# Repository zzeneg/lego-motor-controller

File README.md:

# lego-motor-controller
Control your Lego PF motors with Bluetooth

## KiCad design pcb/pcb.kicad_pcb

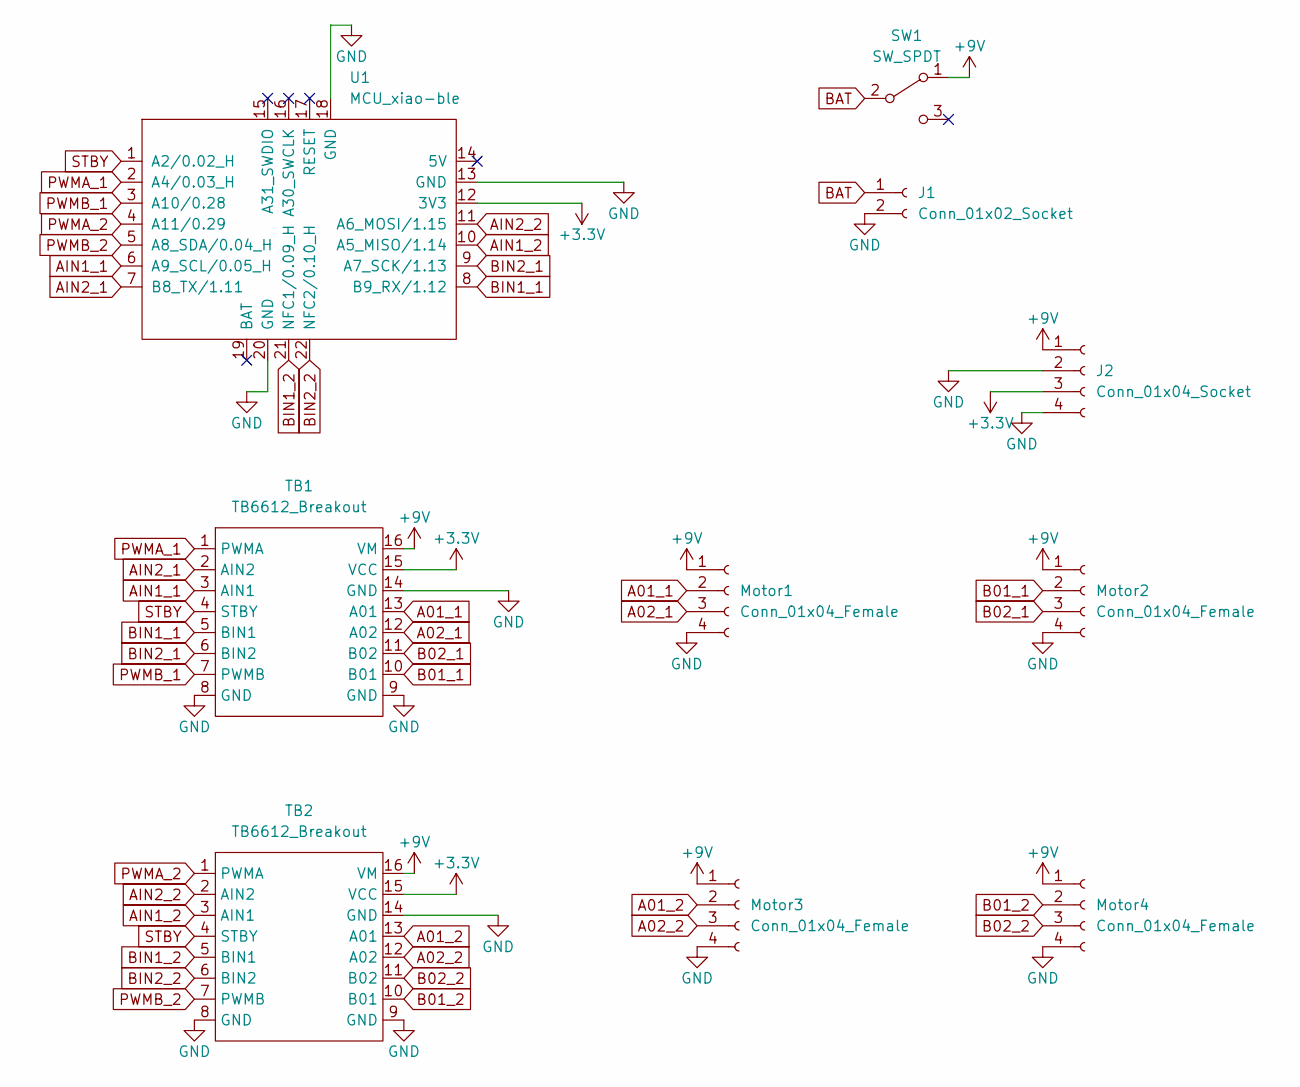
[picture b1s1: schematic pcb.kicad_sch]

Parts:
J1: Conn_01x02_Socket; PinHeader_1x02_P2.54mm_Vertical
J2: Conn_01x04_Socket; voltage-converter
Motor1, Motor2, Motor3, Motor4: Conn_01x04_Female; JST_XH_S4B-XH-A_1x04_P2.50mm_Horizontal
SW1: SW_SPDT; PinHeader_1x03_P2.54mm_Vertical
TB1, TB2: TB6612_Breakout; TB6612-breakout
U1: MCU_xiao-ble; MCU_xiao-ble-smd

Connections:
+3.3V: J2.3, TB1.15 (VCC), TB2.15 (VCC), U1.12 (3V3)
+9V: J2.1, Motor1.1, Motor2.1, Motor3.1, Motor4.1, SW1.1 (A), TB1.16 (VM), TB2.16 (VM)
A01_1: Motor1.2, TB1.13 (A01)
A01_2: Motor3.2, TB2.13 (A01)
A02_1: Motor1.3, TB1.12 (A02)
A02_2: Motor3.3, TB2.12 (A02)
AIN1_1: TB1.3 (AIN1), U1.6 (A9_SCL/0.05_H)
AIN1_2: TB2.3 (AIN1), U1.10 (A5_MISO/1.14)
AIN2_1: TB1.2 (AIN2), U1.7 (B8_TX/1.11)
AIN2_2: TB2.2 (AIN2), U1.11 (A6_MOSI/1.15)
B01_1: Motor2.2, TB1.10 (B01)
B01_2: Motor4.2, TB2.10 (B01)
B02_1: Motor2.3, TB1.11 (B02)
B02_2: Motor4.3, TB2.11 (B02)
BAT: J1.1, SW1.2 (B)
BIN1_1: TB1.5 (BIN1), U1.8 (B9_RX/1.12)
BIN1_2: TB2.5 (BIN1), U1.21 (NFC1/0.09_H)
BIN2_1: TB1.6 (BIN2), U1.9 (A7_SCK/1.13)
BIN2_2: TB2.6 (BIN2), U1.22 (NFC2/0.10_H)
GND: J1.2, J2.2, J2.4, Motor1.4, Motor2.4, Motor3.4, Motor4.4, TB1.8 (GND), TB1.9 (GND), TB1.14 (GND), TB2.8 (GND), TB2.9 (GND), TB2.14 (GND), U1.13 (GND), U1.18 (GND), U1.20 (GND)
PWMA_1: TB1.1 (PWMA), U1.2 (A4/0.03_H)
PWMA_2: TB2.1 (PWMA), U1.4 (A11/0.29)
PWMB_1: TB1.7 (PWMB), U1.3 (A10/0.28)
PWMB_2: TB2.7 (PWMB), U1.5 (A8_SDA/0.04_H)
STBY: TB1.4 (STBY), TB2.4 (STBY), U1.1 (A2/0.02_H)

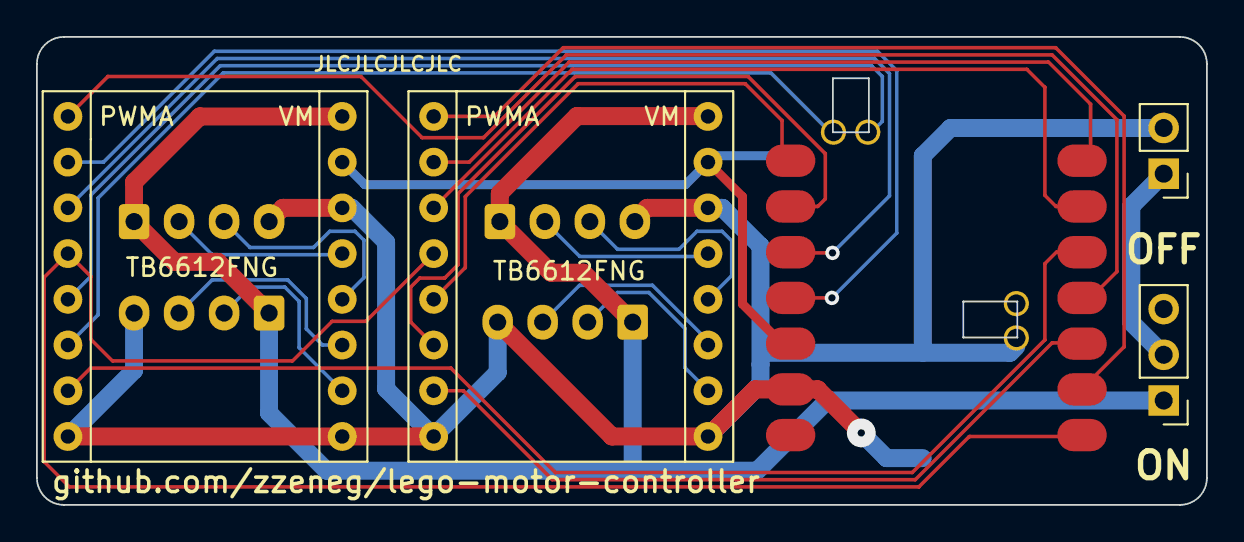
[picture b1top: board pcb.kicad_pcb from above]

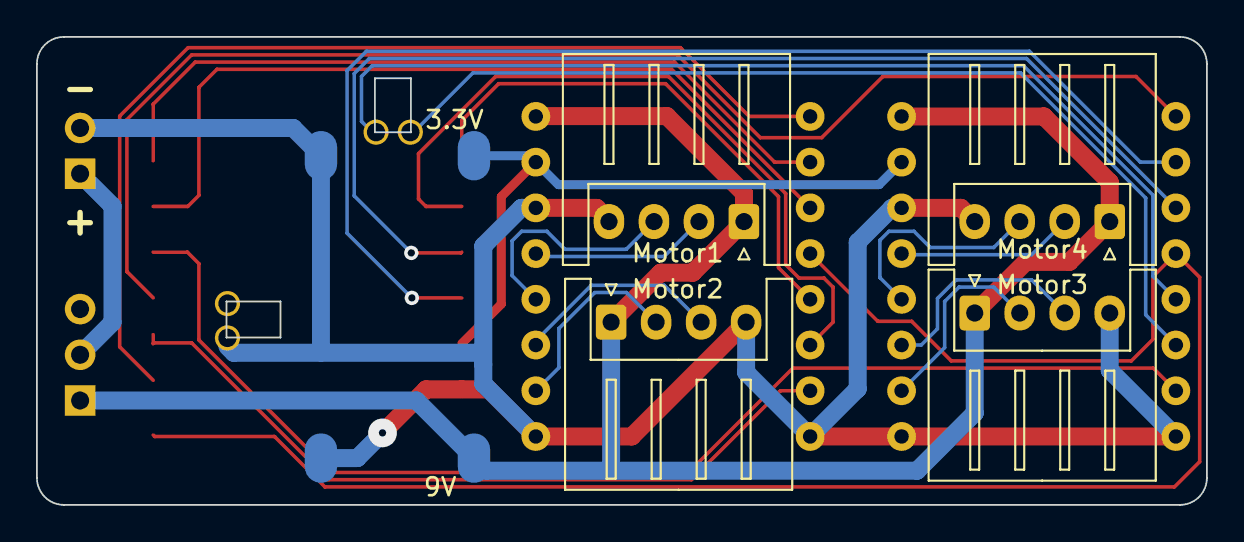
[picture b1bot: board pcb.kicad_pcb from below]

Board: 2 copper layers, 65.0 x 26.0 mm, 10 parts (5 on the bottom side), 25 nets.
